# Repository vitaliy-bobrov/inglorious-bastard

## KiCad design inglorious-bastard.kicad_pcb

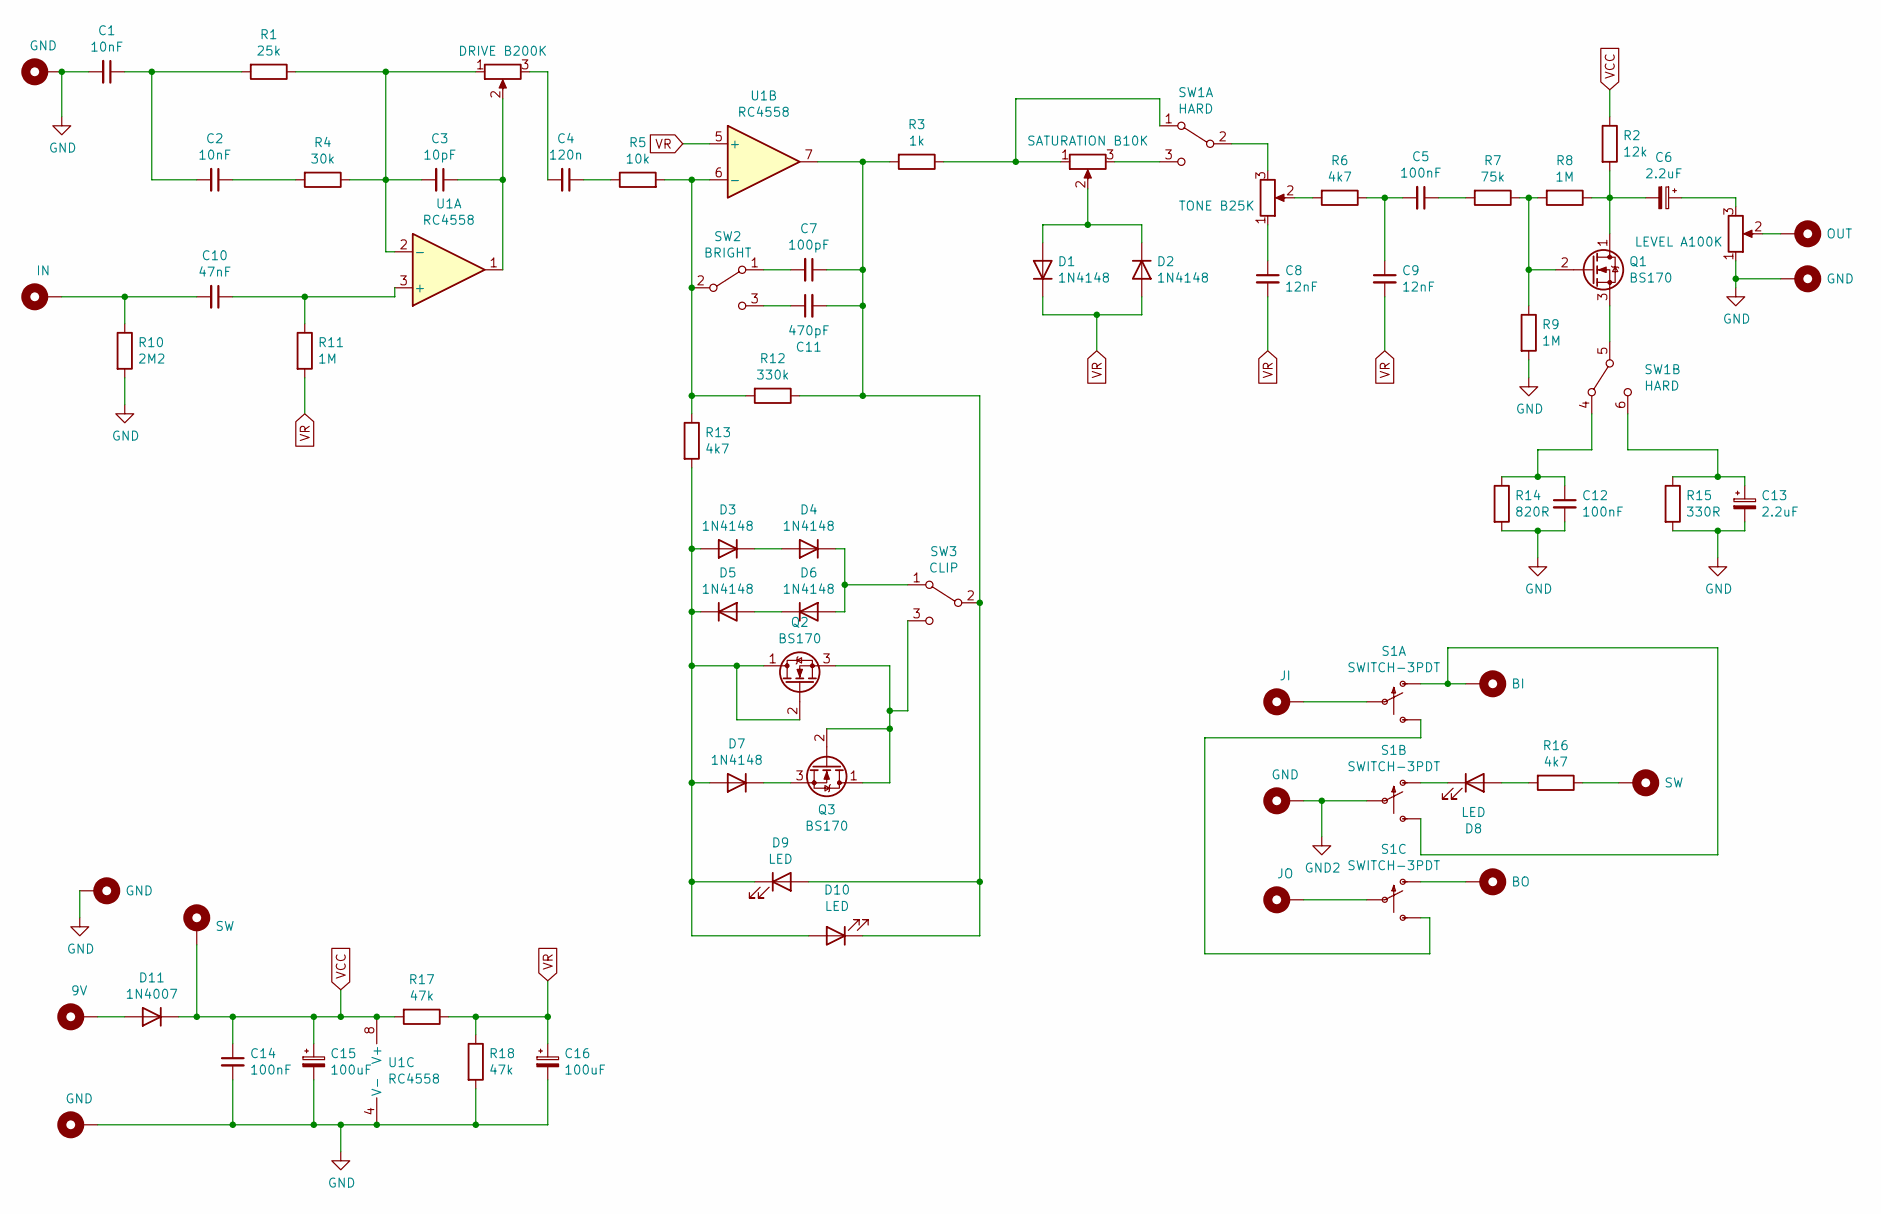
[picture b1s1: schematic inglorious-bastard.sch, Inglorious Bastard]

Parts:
C1, C2: 10nF; 0.2%22.SML
C3: 10pF; 0.1%22
C4: 120n; 0.2%22.SML
C5, C12, C14: 100nF; 0.2%22.SML
C6, C13: 2.2uF; 0501
C7: 100pF; 0.2%22.MED
C8, C9: 12nF; 0.2%22.SML
C10: 47nF; 0.2%22.SML
C11: 470pF; 0.2%22.MED
C15, C16: 100uF; 0503
D1, D2, D3, D4, D5, D6, D7: 1N4148; DO35-3
D8: LED; 3MM_IO
D9, D10: LED; 3MM_1
D11: 1N4007; DO41-3
H1, H3, H8, H10, H14: GND; PAD3
H2: OUT; PAD1
H4: IN; PAD1
H5: BI; PAD3
H6: JI; PAD3
H7: SW; PAD1
H9: BO; PAD3
H11: JO; PAD3
H12: SW; PAD3
H13: 9V; PAD3
Q1, Q2, Q3: BS170; TO92
R1: 25k; 0.3%22.B
R2: 12k; 0.3%22.B
R3: 1k; 0.3%22.B
R4: 30k; 0.3%22.B
R5: 10k; 0.3%22.B
R6, R13, R16: 4k7; 0.3%22.B
R7: 75k; 0.3%22.B
R8, R9, R11: 1M; 0.3%22.B
R10: 2M2; 0.3%22.B
R12: 330k; 0.3%22.B
R14: 820R; 0.3%22.B
R15: 330R; 0.3%22.B
R17, R18: 47k; 0.3%22.B
RV1: DRIVE B200K; 16MM_B.MOUNT
RV2: SATURATION B10K; 16MM_B.MOUNT
RV3: TONE B25K; 16MM_B.MOUNT
RV4: LEVEL A100K; 16MM_B.MOUNT
S1: SWITCH-3PDT; 3PDT.LUGS.SPF
SW1: HARD; DPDT.LUGS
SW2: BRIGHT; SPDT.LUGS
SW3: CLIP; SPDT.LUGS
U1: RC4558; DIP08

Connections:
GND: C1.2, C12.2, C13.2, C14.2, C15.2, C16.2, H1.1, H3.1, H10.1, H14.1, R9.2, R10.2, R14.2, R15.2, R18.2, RV4.1, U1.4 (V-)
GND2: H8.1, S1.P$5
unnamed: C1.1, C2.2, R1.2
unnamed: C2.1, R4.2
unnamed: C3.1, RV1.2, U1.1
unnamed: C3.2, R1.1, R4.1, RV1.1, U1.2 (-)
unnamed: C4.1, R5.1
unnamed: C4.2, RV1.3
unnamed: C5.1, R7.2
unnamed: C5.2, C9.1, R6.1
unnamed: C6.1, RV4.3
unnamed: C6.2, Q1.1 (D), R2.2, R8.1
unnamed: C7.2, SW2.1 (A)
unnamed: C8.1, RV3.1
unnamed: C10.1, R11.1, U1.3 (+)
unnamed: C10.2, H4.1, R10.1
unnamed: C11.1, SW2.3 (C)
unnamed: C7.1, C11.2, D9.2 (A), D10.1 (K), R3.2, R12.1, SW3.2 (B), U1.7
unnamed: C12.1, R14.1, SW1.4 (A)
unnamed: C13.1, R15.1, SW1.6 (C)
unnamed: D1.2 (A), D2.1 (K), RV2.2
unnamed: D3.1 (K), D4.2 (A)
unnamed: D4.1 (K), D6.2 (A), SW3.1 (A)
unnamed: D5.2 (A), D6.1 (K)
unnamed: D7.1 (K), Q3.3 (S)
unnamed: D8.1 (K), S1.P$4 (O)
unnamed: D8.2 (A), R16.2
unnamed: D3.2 (A), D5.1 (K), D7.2 (A), D9.1 (K), D10.2 (A), Q2.1 (D), Q2.2 (G), R13.2
unnamed: D11.2 (A), H13.1
unnamed: H2.1, RV4.2
unnamed: H5.1, S1.P$1 (O), S1.P$6 (S)
unnamed: H6.1, S1.P$2
unnamed: H7.1, R16.1
unnamed: H9.1, S1.P$7 (O)
unnamed: H11.1, S1.P$8
unnamed: Q1.2 (G), R7.1, R8.2, R9.1
unnamed: Q1.3 (S), SW1.5 (B)
unnamed: Q2.3 (S), Q3.1 (D), Q3.2 (G), SW3.3 (C)
unnamed: R3.1, RV2.1, SW1.1 (A)
unnamed: R6.2, RV3.2
unnamed: R5.2, R12.2, R13.1, SW2.2 (B), U1.6 (-)
unnamed: RV2.3, SW1.3 (C)
unnamed: RV3.3, SW1.2 (B)
unnamed: S1.P$3 (S), S1.P$9 (S)
VCC: C14.1, C15.1, D11.1 (K), H12.1, R2.1, R17.2, U1.8 (V+)
VR: C8.2, C9.2, C16.1, D1.1 (K), D2.2 (A), R11.2, R17.1, R18.1, U1.5 (+)

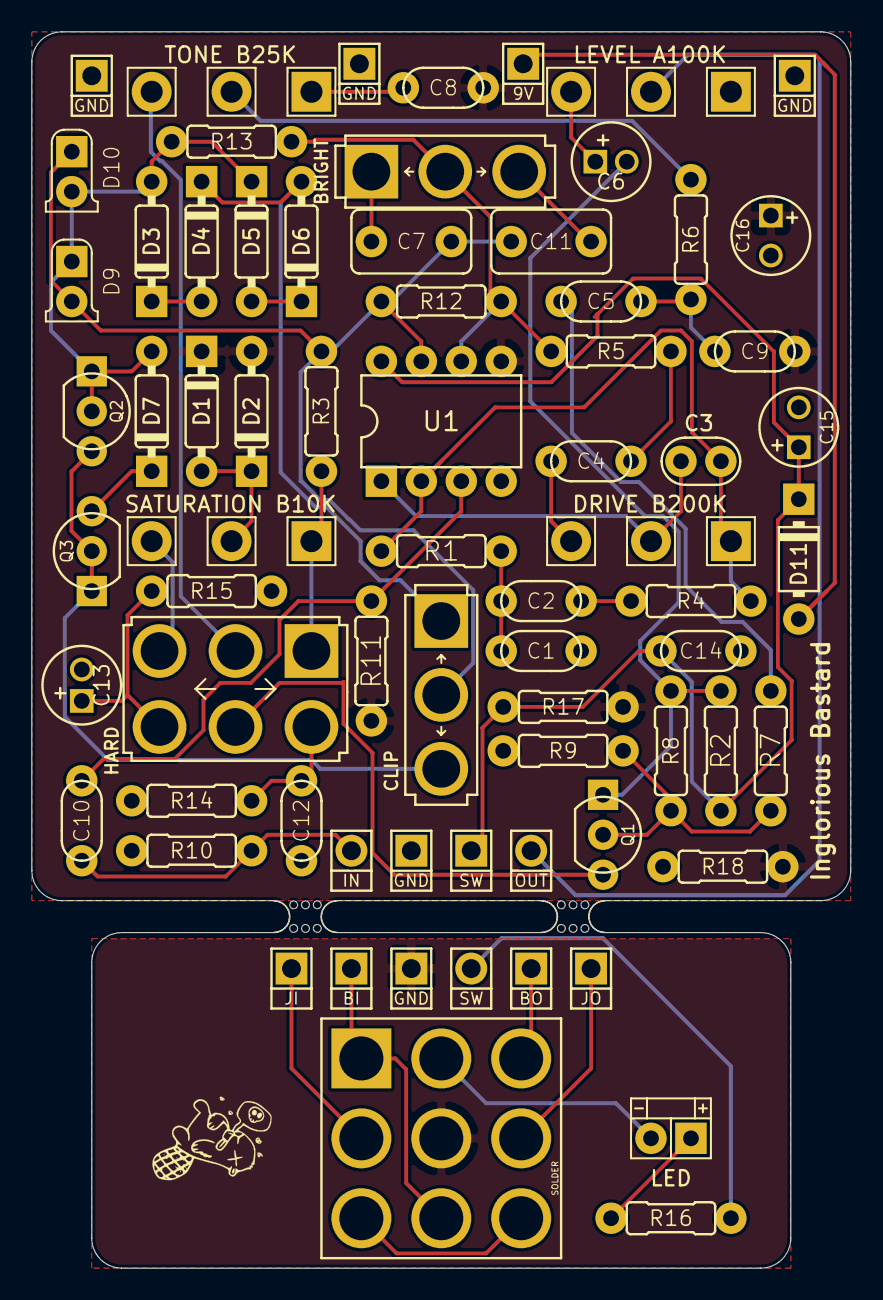
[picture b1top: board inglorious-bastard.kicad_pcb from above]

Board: 2 copper layers, 52.1 x 78.6 mm, 76 parts (0 on the bottom side), 46 nets.

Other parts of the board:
JOUT4, JOUT4#2: LUMBURG_DRILL
Ref**: Val**; DC_TOP
mouse-bite-2mm-slot, mouse-bite-2mm-slot#2: VAL**; mouse-bite-2mm-slot

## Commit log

2020-10-21 v1.0
2020-10-21 rename readme file
